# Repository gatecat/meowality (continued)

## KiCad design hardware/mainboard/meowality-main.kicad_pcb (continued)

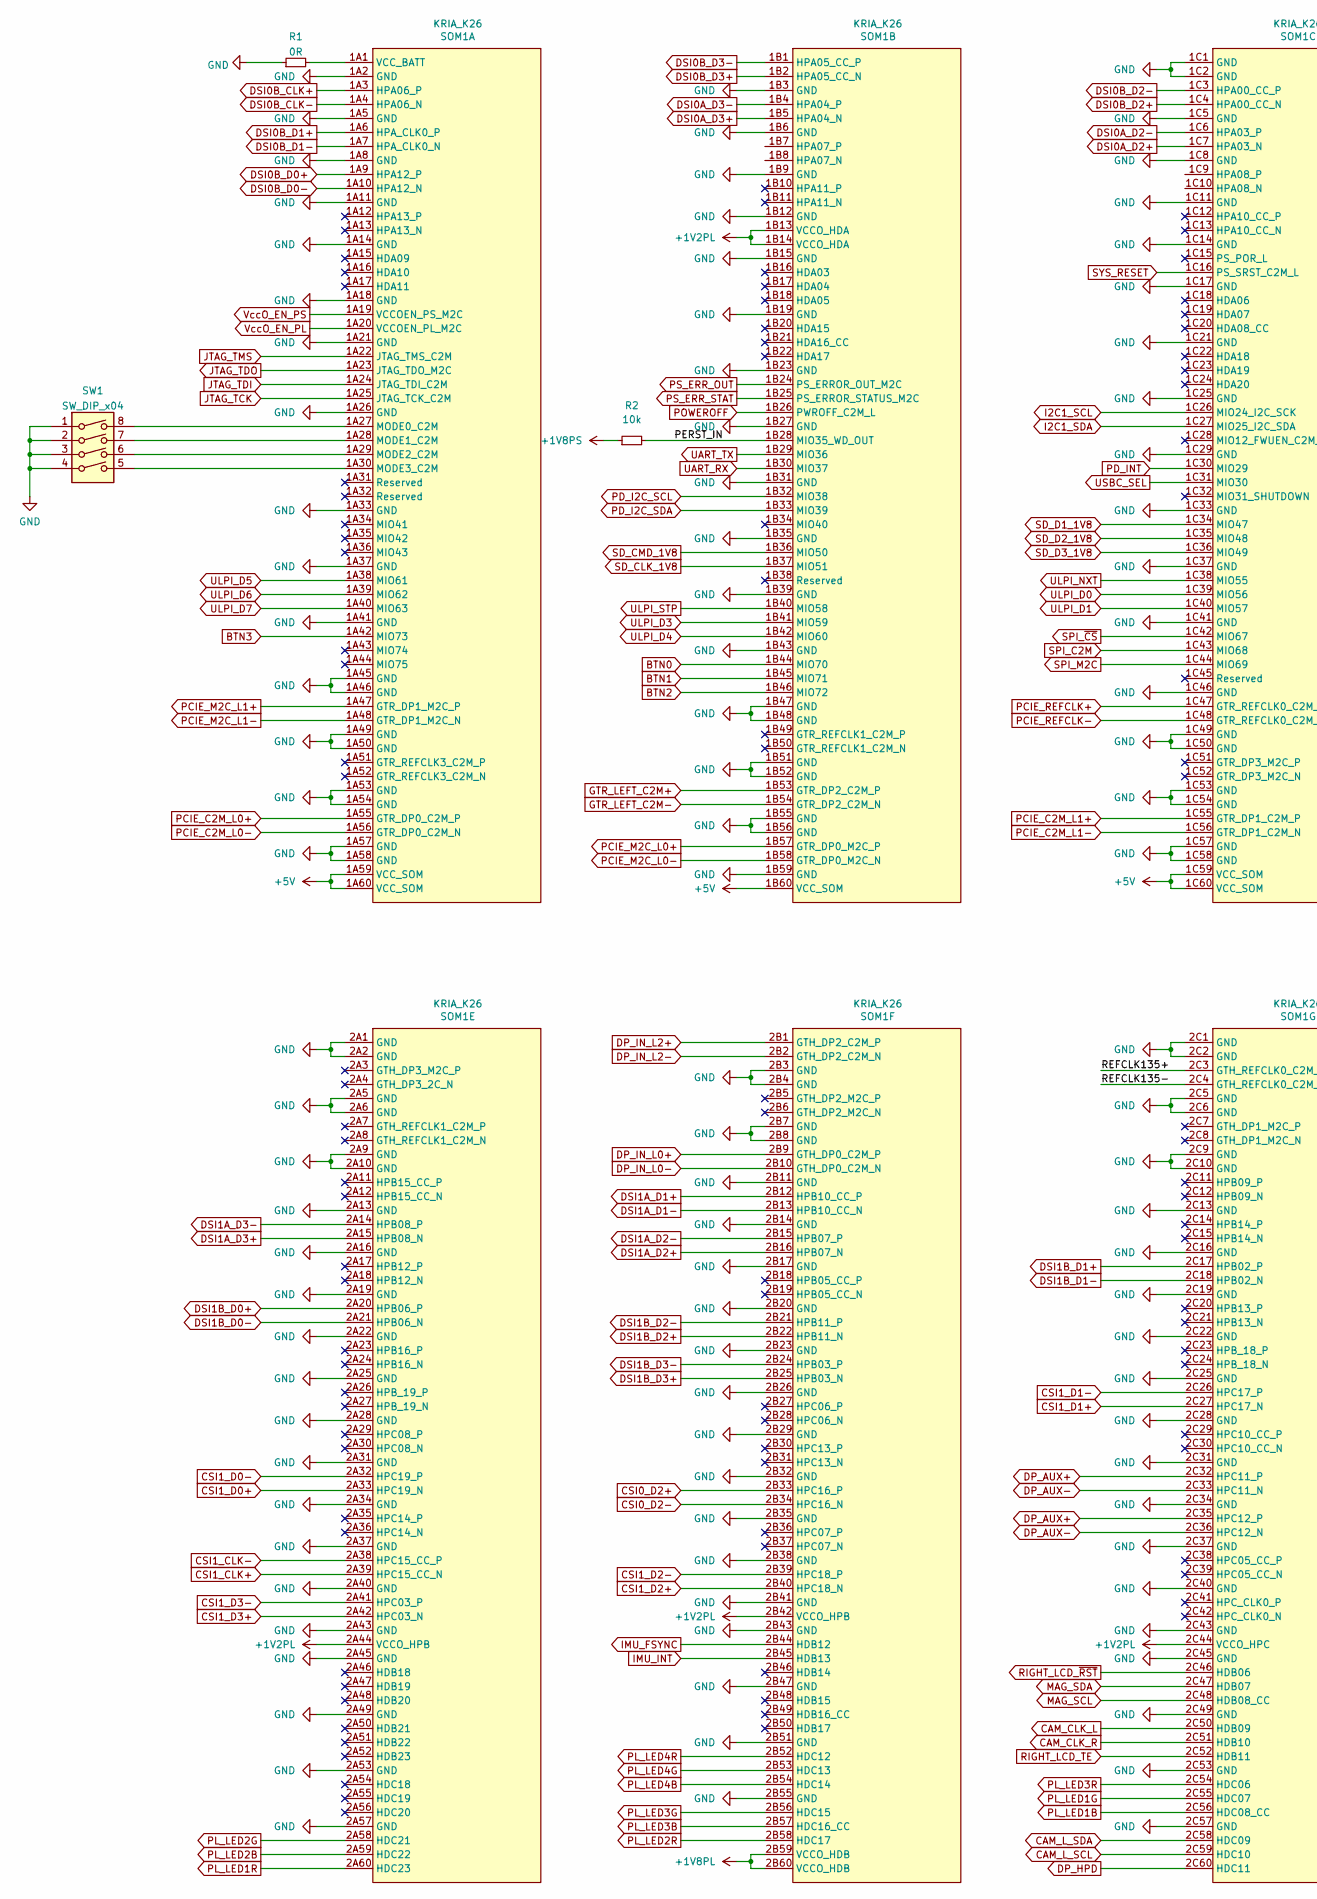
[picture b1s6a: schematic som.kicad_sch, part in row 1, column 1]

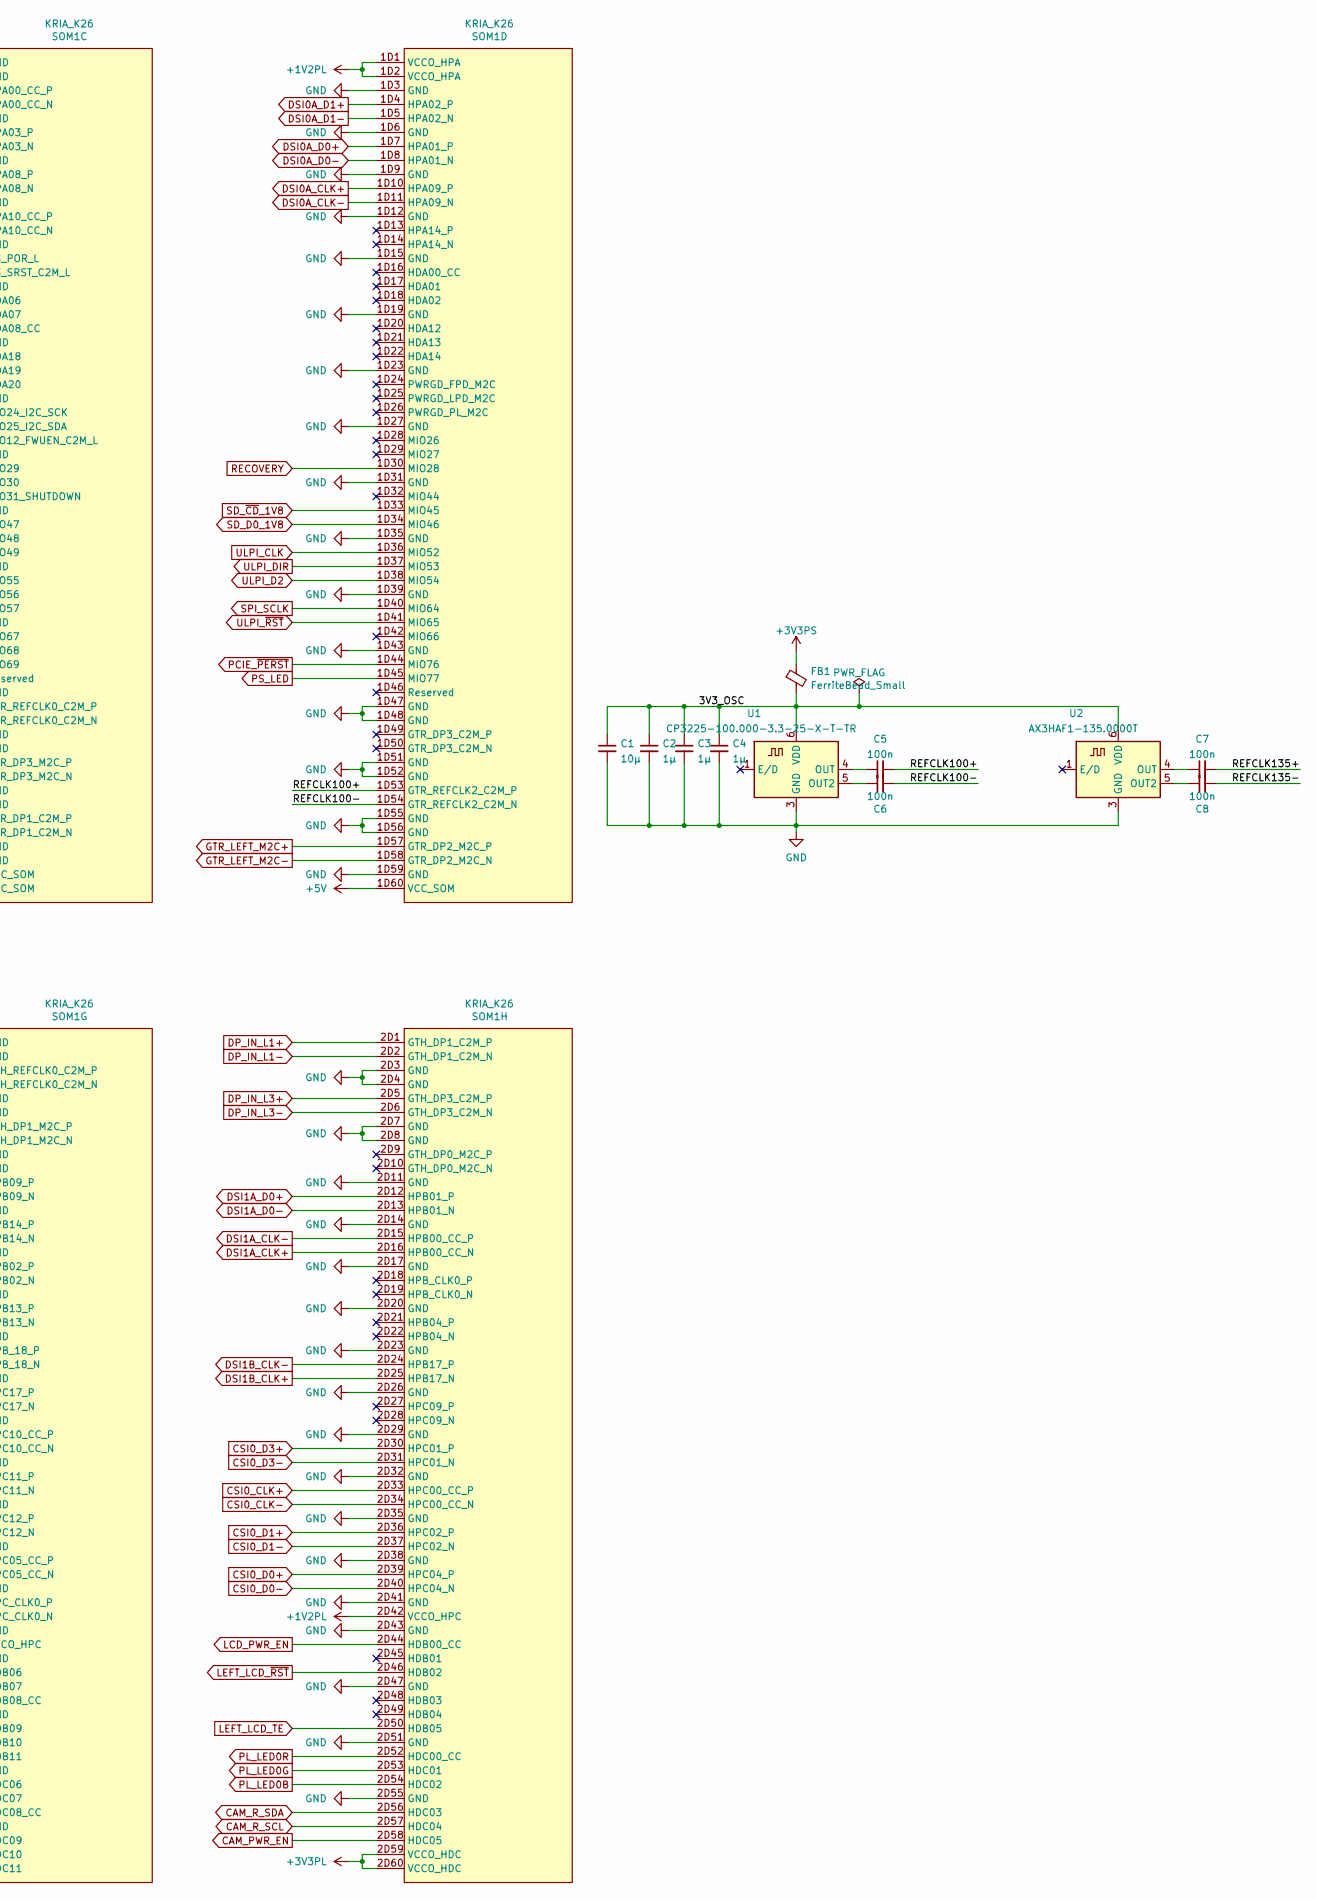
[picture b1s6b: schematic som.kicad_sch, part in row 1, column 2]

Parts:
C1: 10µ; C_1206_3216Metric
C2, C3, C4: 1µ; C_0603_1608Metric
C5, C6, C7, C8: 100n; C_0402_1005Metric
FB1: FerriteBead_Small; L_0603_1608Metric
R1: 0R; R_0402_1005Metric
R2: 10k; R_0402_1005Metric
SOM1: KRIA_K26
SW1: SW_DIP_x04; SW_DIP_SPSTx04_Slide_Copal_CHS-04B_W7.62mm_P1.27mm
U1: CP3225-100.000-3.3-25-X-T-TR; Oscillator_SMD_IDT_JS6-6_5.0x3.2mm_P1.27mm
U2: AX3HAF1-135.0000T; Oscillator_SMD_IDT_JS6-6_5.0x3.2mm_P1.27mm

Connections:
+1V2PL: SOM1.1B13 (VCCO_HDA), SOM1.1B14 (VCCO_HDA), SOM1.1D1 (VCCO_HPA), SOM1.1D2 (VCCO_HPA), SOM1.2A44 (VCCO_HPB), SOM1.2B42 (VCCO_HPB), SOM1.2C44 (VCCO_HPC), SOM1.2D42 (VCCO_HPC); also elsewhere on the board
+1V8PL: SOM1.2B59 (VCCO_HDB), SOM1.2B60 (VCCO_HDB); also elsewhere on the board
+1V8PS: R2.1; also elsewhere on the board
+3V3PL: SOM1.2D59 (VCCO_HDC), SOM1.2D60 (VCCO_HDC); also elsewhere on the board
+3V3PS: FB1.1; also elsewhere on the board
+5V: SOM1.1A59 (VCC_SOM), SOM1.1A60 (VCC_SOM), SOM1.1B60 (VCC_SOM), SOM1.1C59 (VCC_SOM), SOM1.1C60 (VCC_SOM), SOM1.1D60 (VCC_SOM); also elsewhere on the board
/SOM/3V3_OSC: C1.1, C2.1, C3.1, C4.1, FB1.2, U1.6 (VDD), U2.6 (VDD)
/SOM/PERST_IN: R2.2, SOM1.1B28 (MIO35_WD_OUT)
/SOM/REFCLK100+: C5.2, SOM1.1D53 (GTR_REFCLK2_C2M_P)
/SOM/REFCLK100-: C6.2, SOM1.1D54 (GTR_REFCLK2_C2M_N)
/SOM/REFCLK135+: C7.2, SOM1.2C3 (GTH_REFCLK0_C2M_P)
/SOM/REFCLK135-: C8.2, SOM1.2C4 (GTH_REFCLK0_C2M_N)
BTN0: SOM1.1B44 (MIO70); also elsewhere on the board
BTN1: SOM1.1B45 (MIO71); also elsewhere on the board
BTN2: SOM1.1B46 (MIO72); also elsewhere on the board
BTN3: SOM1.1A42 (MIO73); also elsewhere on the board
CAM_CLK_L: SOM1.2C50 (HDB09); also elsewhere on the board
CAM_CLK_R: SOM1.2C51 (HDB10); also elsewhere on the board
CAM_L_SCL: SOM1.2C59 (HDC10); also elsewhere on the board
CAM_L_SDA: SOM1.2C58 (HDC09); also elsewhere on the board
CAM_PWR_EN: SOM1.2D58 (HDC05); also elsewhere on the board
CAM_R_SCL: SOM1.2D57 (HDC04); also elsewhere on the board
CAM_R_SDA: SOM1.2D56 (HDC03); also elsewhere on the board
CSI0_CLK+: SOM1.2D33 (HPC00_CC_P); also elsewhere on the board
CSI0_CLK-: SOM1.2D34 (HPC00_CC_N); also elsewhere on the board
CSI0_D0+: SOM1.2D39 (HPC04_P); also elsewhere on the board
CSI0_D0-: SOM1.2D40 (HPC04_N); also elsewhere on the board
CSI0_D1+: SOM1.2D36 (HPC02_P); also elsewhere on the board
CSI0_D1-: SOM1.2D37 (HPC02_N); also elsewhere on the board
CSI0_D2+: SOM1.2B33 (HPC16_P); also elsewhere on the board
CSI0_D2-: SOM1.2B34 (HPC16_N); also elsewhere on the board
CSI0_D3+: SOM1.2D30 (HPC01_P); also elsewhere on the board
CSI0_D3-: SOM1.2D31 (HPC01_N); also elsewhere on the board
CSI1_CLK+: SOM1.2A39 (HPC15_CC_N); also elsewhere on the board
CSI1_CLK-: SOM1.2A38 (HPC15_CC_P); also elsewhere on the board
CSI1_D0+: SOM1.2A33 (HPC19_N); also elsewhere on the board
CSI1_D0-: SOM1.2A32 (HPC19_P); also elsewhere on the board
CSI1_D1+: SOM1.2C27 (HPC17_N); also elsewhere on the board
CSI1_D1-: SOM1.2C26 (HPC17_P); also elsewhere on the board
CSI1_D2+: SOM1.2B40 (HPC18_N); also elsewhere on the board
CSI1_D2-: SOM1.2B39 (HPC18_P); also elsewhere on the board
CSI1_D3+: SOM1.2A42 (HPC03_N); also elsewhere on the board
CSI1_D3-: SOM1.2A41 (HPC03_P); also elsewhere on the board
DP_AUX+: SOM1.2C32 (HPC11_P), SOM1.2C35 (HPC12_P); also elsewhere on the board
DP_AUX-: SOM1.2C33 (HPC11_N), SOM1.2C36 (HPC12_N); also elsewhere on the board
DP_HPD: SOM1.2C60 (HDC11); also elsewhere on the board
DP_IN_L0+: SOM1.2B9 (GTH_DP0_C2M_P); also elsewhere on the board
DP_IN_L0-: SOM1.2B10 (GTH_DP0_C2M_N); also elsewhere on the board
DP_IN_L1+: SOM1.2D1 (GTH_DP1_C2M_P); also elsewhere on the board
DP_IN_L1-: SOM1.2D2 (GTH_DP1_C2M_N); also elsewhere on the board
DP_IN_L2+: SOM1.2B1 (GTH_DP2_C2M_P); also elsewhere on the board
DP_IN_L2-: SOM1.2B2 (GTH_DP2_C2M_N); also elsewhere on the board
DP_IN_L3+: SOM1.2D5 (GTH_DP3_C2M_P); also elsewhere on the board
DP_IN_L3-: SOM1.2D6 (GTH_DP3_C2M_N); also elsewhere on the board
DSI0A_CLK+: SOM1.1D10 (HPA09_P); also elsewhere on the board
DSI0A_CLK-: SOM1.1D11 (HPA09_N); also elsewhere on the board
DSI0A_D0+: SOM1.1D7 (HPA01_P); also elsewhere on the board
DSI0A_D0-: SOM1.1D8 (HPA01_N); also elsewhere on the board
DSI0A_D1+: SOM1.1D4 (HPA02_P); also elsewhere on the board
DSI0A_D1-: SOM1.1D5 (HPA02_N); also elsewhere on the board
DSI0A_D2+: SOM1.1C7 (HPA03_N); also elsewhere on the board
DSI0A_D2-: SOM1.1C6 (HPA03_P); also elsewhere on the board
DSI0A_D3+: SOM1.1B5 (HPA04_N); also elsewhere on the board
DSI0A_D3-: SOM1.1B4 (HPA04_P); also elsewhere on the board
DSI0B_CLK+: SOM1.1A3 (HPA06_P); also elsewhere on the board
DSI0B_CLK-: SOM1.1A4 (HPA06_N); also elsewhere on the board
DSI0B_D0+: SOM1.1A9 (HPA12_P); also elsewhere on the board
DSI0B_D0-: SOM1.1A10 (HPA12_N); also elsewhere on the board
DSI0B_D1+: SOM1.1A6 (HPA_CLK0_P); also elsewhere on the board
DSI0B_D1-: SOM1.1A7 (HPA_CLK0_N); also elsewhere on the board
DSI0B_D2+: SOM1.1C4 (HPA00_CC_N); also elsewhere on the board
DSI0B_D2-: SOM1.1C3 (HPA00_CC_P); also elsewhere on the board
DSI0B_D3+: SOM1.1B2 (HPA05_CC_N); also elsewhere on the board
DSI0B_D3-: SOM1.1B1 (HPA05_CC_P); also elsewhere on the board
DSI1A_CLK+: SOM1.2D16 (HPB00_CC_N); also elsewhere on the board
DSI1A_CLK-: SOM1.2D15 (HPB00_CC_P); also elsewhere on the board
DSI1A_D0+: SOM1.2D12 (HPB01_P); also elsewhere on the board
DSI1A_D0-: SOM1.2D13 (HPB01_N); also elsewhere on the board
DSI1A_D1+: SOM1.2B12 (HPB10_CC_P); also elsewhere on the board
DSI1A_D1-: SOM1.2B13 (HPB10_CC_N); also elsewhere on the board
DSI1A_D2+: SOM1.2B16 (HPB07_N); also elsewhere on the board
DSI1A_D2-: SOM1.2B15 (HPB07_P); also elsewhere on the board
DSI1A_D3+: SOM1.2A15 (HPB08_N); also elsewhere on the board
DSI1A_D3-: SOM1.2A14 (HPB08_P); also elsewhere on the board
DSI1B_CLK+: SOM1.2D25 (HPB17_N); also elsewhere on the board
DSI1B_CLK-: SOM1.2D24 (HPB17_P); also elsewhere on the board
DSI1B_D0+: SOM1.2A20 (HPB06_P); also elsewhere on the board
DSI1B_D0-: SOM1.2A21 (HPB06_N); also elsewhere on the board
DSI1B_D1+: SOM1.2C17 (HPB02_P); also elsewhere on the board
DSI1B_D1-: SOM1.2C18 (HPB02_N); also elsewhere on the board
DSI1B_D2+: SOM1.2B22 (HPB11_N); also elsewhere on the board
DSI1B_D2-: SOM1.2B21 (HPB11_P); also elsewhere on the board
DSI1B_D3+: SOM1.2B25 (HPB03_N); also elsewhere on the board
DSI1B_D3-: SOM1.2B24 (HPB03_P); also elsewhere on the board
GND: C1.2, C2.2, C3.2, C4.2, R1.1, SOM1.1A2 (GND), SOM1.1A5 (GND), SOM1.1A8 (GND), SOM1.1A11 (GND), SOM1.1A14 (GND), SOM1.1A18 (GND), SOM1.1A21 (GND), SOM1.1A26 (GND), SOM1.1A33 (GND), SOM1.1A37 (GND), SOM1.1A41 (GND), SOM1.1A45 (GND), SOM1.1A46 (GND), SOM1.1A49 (GND), SOM1.1A50 (GND), SOM1.1A53 (GND), SOM1.1A54 (GND), SOM1.1A57 (GND), SOM1.1A58 (GND), SOM1.1B3 (GND), SOM1.1B6 (GND), SOM1.1B9 (GND), SOM1.1B12 (GND), SOM1.1B15 (GND), SOM1.1B19 (GND), SOM1.1B23 (GND), SOM1.1B27 (GND), SOM1.1B31 (GND), SOM1.1B35 (GND), SOM1.1B39 (GND), SOM1.1B43 (GND), SOM1.1B47 (GND), SOM1.1B48 (GND), SOM1.1B51 (GND), SOM1.1B52 (GND), SOM1.1B55 (GND), SOM1.1B56 (GND), SOM1.1B59 (GND), SOM1.1C1 (GND), SOM1.1C2 (GND), SOM1.1C5 (GND), SOM1.1C8 (GND), SOM1.1C11 (GND), SOM1.1C14 (GND), SOM1.1C17 (GND), SOM1.1C21 (GND), SOM1.1C25 (GND), SOM1.1C29 (GND), SOM1.1C33 (GND), SOM1.1C37 (GND), SOM1.1C41 (GND), SOM1.1C46 (GND), SOM1.1C49 (GND), SOM1.1C50 (GND), SOM1.1C53 (GND), SOM1.1C54 (GND), SOM1.1C57 (GND), SOM1.1C58 (GND), SOM1.1D3 (GND), SOM1.1D6 (GND), SOM1.1D9 (GND), SOM1.1D12 (GND), SOM1.1D15 (GND), SOM1.1D19 (GND), SOM1.1D23 (GND), SOM1.1D27 (GND), SOM1.1D31 (GND), SOM1.1D35 (GND), SOM1.1D39 (GND), SOM1.1D43 (GND), SOM1.1D47 (GND), SOM1.1D48 (GND), SOM1.1D51 (GND), SOM1.1D52 (GND), SOM1.1D55 (GND), SOM1.1D56 (GND), SOM1.1D59 (GND), SOM1.2A1 (GND), SOM1.2A2 (GND), SOM1.2A5 (GND), SOM1.2A6 (GND), SOM1.2A9 (GND), SOM1.2A10 (GND), SOM1.2A13 (GND), SOM1.2A16 (GND), SOM1.2A19 (GND), SOM1.2A22 (GND), SOM1.2A25 (GND), SOM1.2A28 (GND), SOM1.2A31 (GND), SOM1.2A34 (GND), SOM1.2A37 (GND), SOM1.2A40 (GND), SOM1.2A43 (GND), SOM1.2A45 (GND), SOM1.2A49 (GND), SOM1.2A53 (GND), SOM1.2A57 (GND), SOM1.2B3 (GND), SOM1.2B4 (GND), SOM1.2B7 (GND), SOM1.2B8 (GND), SOM1.2B11 (GND), SOM1.2B14 (GND), SOM1.2B17 (GND), SOM1.2B20 (GND), SOM1.2B23 (GND), SOM1.2B26 (GND), SOM1.2B29 (GND), SOM1.2B32 (GND), SOM1.2B35 (GND), SOM1.2B38 (GND), SOM1.2B41 (GND), SOM1.2B43 (GND), SOM1.2B47 (GND), SOM1.2B51 (GND), SOM1.2B55 (GND), SOM1.2C1 (GND), SOM1.2C2 (GND), SOM1.2C5 (GND), SOM1.2C6 (GND), SOM1.2C9 (GND), SOM1.2C10 (GND), SOM1.2C13 (GND), SOM1.2C16 (GND), SOM1.2C19 (GND), SOM1.2C22 (GND), SOM1.2C25 (GND), SOM1.2C28 (GND), SOM1.2C31 (GND), SOM1.2C34 (GND), SOM1.2C37 (GND), SOM1.2C40 (GND), SOM1.2C43 (GND), SOM1.2C45 (GND), SOM1.2C49 (GND), SOM1.2C53 (GND), SOM1.2C57 (GND), SOM1.2D3 (GND), SOM1.2D4 (GND), SOM1.2D7 (GND), SOM1.2D8 (GND), SOM1.2D11 (GND), SOM1.2D14 (GND), SOM1.2D17 (GND), SOM1.2D20 (GND), SOM1.2D23 (GND), SOM1.2D26 (GND), SOM1.2D29 (GND), SOM1.2D32 (GND), SOM1.2D35 (GND), SOM1.2D38 (GND), SOM1.2D41 (GND), SOM1.2D43 (GND), SOM1.2D47 (GND), SOM1.2D51 (GND), SOM1.2D55 (GND), SW1.1, SW1.2, SW1.3, SW1.4, U1.3 (GND), U2.3 (GND); also elsewhere on the board
GTR_LEFT_C2M+: SOM1.1B53 (GTR_DP2_C2M_P); also elsewhere on the board
GTR_LEFT_C2M-: SOM1.1B54 (GTR_DP2_C2M_N); also elsewhere on the board
GTR_LEFT_M2C+: SOM1.1D57 (GTR_DP2_M2C_P); also elsewhere on the board
GTR_LEFT_M2C-: SOM1.1D58 (GTR_DP2_M2C_N); also elsewhere on the board
I2C1_SCL: SOM1.1C26 (MIO24_I2C_SCK); also elsewhere on the board
I2C1_SDA: SOM1.1C27 (MIO25_I2C_SDA); also elsewhere on the board
IMU_FSYNC: SOM1.2B44 (HDB12); also elsewhere on the board
IMU_INT: SOM1.2B45 (HDB13); also elsewhere on the board
JTAG_TCK: SOM1.1A25 (JTAG_TCK_C2M); also elsewhere on the board
JTAG_TDI: SOM1.1A24 (JTAG_TDI_C2M); also elsewhere on the board
JTAG_TDO: SOM1.1A23 (JTAG_TDO_M2C); also elsewhere on the board
JTAG_TMS: SOM1.1A22 (JTAG_TMS_C2M); also elsewhere on the board
LCD_PWR_EN: SOM1.2D44 (HDB00_CC); also elsewhere on the board
LEFT_LCD_TE: SOM1.2D50 (HDB05); also elsewhere on the board
LEFT_LCD_~RST: SOM1.2D46 (HDB02); also elsewhere on the board
MAG_SCL: SOM1.2C48 (HDB08_CC); also elsewhere on the board
MAG_SDA: SOM1.2C47 (HDB07); also elsewhere on the board
unnamed: C5.1, U1.4 (OUT)
unnamed: C6.1, U1.5 (OUT2)
unnamed: C7.1, U2.4 (OUT)
unnamed: C8.1, U2.5 (OUT2)
unnamed: R1.2, SOM1.1A1 (VCC_BATT)
unnamed: SOM1.1A27 (MODE0_C2M), SW1.8
unnamed: SOM1.1A28 (MODE1_C2M), SW1.7
unnamed: SOM1.1A29 (MODE2_C2M), SW1.6
unnamed: SOM1.1A30 (MODE3_C2M), SW1.5
PCIE_C2M_L0+: SOM1.1A55 (GTR_DP0_C2M_P); also elsewhere on the board
PCIE_C2M_L0-: SOM1.1A56 (GTR_DP0_C2M_N); also elsewhere on the board
PCIE_C2M_L1+: SOM1.1C55 (GTR_DP1_C2M_P); also elsewhere on the board
PCIE_C2M_L1-: SOM1.1C56 (GTR_DP1_C2M_N); also elsewhere on the board
PCIE_M2C_L0+: SOM1.1B57 (GTR_DP0_M2C_P); also elsewhere on the board
PCIE_M2C_L0-: SOM1.1B58 (GTR_DP0_M2C_N); also elsewhere on the board
PCIE_M2C_L1+: SOM1.1A47 (GTR_DP1_M2C_P); also elsewhere on the board
PCIE_M2C_L1-: SOM1.1A48 (GTR_DP1_M2C_N); also elsewhere on the board
PCIE_REFCLK+: SOM1.1C47 (GTR_REFCLK0_C2M_P); also elsewhere on the board
PCIE_REFCLK-: SOM1.1C48 (GTR_REFCLK0_C2M_N); also elsewhere on the board
PCIE_~PERST: SOM1.1D44 (MIO76); also elsewhere on the board
PD_I2C_SCL: SOM1.1B32 (MIO38); also elsewhere on the board
PD_I2C_SDA: SOM1.1B33 (MIO39); also elsewhere on the board
PD_INT: SOM1.1C30 (MIO29); also elsewhere on the board
PL_LED0B: SOM1.2D54 (HDC02); also elsewhere on the board
PL_LED0G: SOM1.2D53 (HDC01); also elsewhere on the board
PL_LED0R: SOM1.2D52 (HDC00_CC); also elsewhere on the board
PL_LED1B: SOM1.2C56 (HDC08_CC); also elsewhere on the board
PL_LED1G: SOM1.2C55 (HDC07); also elsewhere on the board
PL_LED1R: SOM1.2A60 (HDC23); also elsewhere on the board
PL_LED2B: SOM1.2A59 (HDC22); also elsewhere on the board
PL_LED2G: SOM1.2A58 (HDC21); also elsewhere on the board
PL_LED2R: SOM1.2B58 (HDC17); also elsewhere on the board
PL_LED3B: SOM1.2B57 (HDC16_CC); also elsewhere on the board
PL_LED3G: SOM1.2B56 (HDC15); also elsewhere on the board
PL_LED3R: SOM1.2C54 (HDC06); also elsewhere on the board
PL_LED4B: SOM1.2B54 (HDC14); also elsewhere on the board
PL_LED4G: SOM1.2B53 (HDC13); also elsewhere on the board
PL_LED4R: SOM1.2B52 (HDC12); also elsewhere on the board
POWEROFF: SOM1.1B26 (PWROFF_C2M_L); also elsewhere on the board
PS_ERR_OUT: SOM1.1B24 (PS_ERROR_OUT_M2C); also elsewhere on the board
PS_ERR_STAT: SOM1.1B25 (PS_ERROR_STATUS_M2C); also elsewhere on the board
PS_LED: SOM1.1D45 (MIO77); also elsewhere on the board
RECOVERY: SOM1.1D30 (MIO28); also elsewhere on the board
RIGHT_LCD_TE: SOM1.2C52 (HDB11); also elsewhere on the board
RIGHT_LCD_~RST: SOM1.2C46 (HDB06); also elsewhere on the board
SD_CLK_1V8: SOM1.1B37 (MIO51); also elsewhere on the board
SD_CMD_1V8: SOM1.1B36 (MIO50); also elsewhere on the board
SD_D0_1V8: SOM1.1D34 (MIO46); also elsewhere on the board
SD_D1_1V8: SOM1.1C34 (MIO47); also elsewhere on the board
SD_D2_1V8: SOM1.1C35 (MIO48); also elsewhere on the board
SD_D3_1V8: SOM1.1C36 (MIO49); also elsewhere on the board
SD_~CD_1V8: SOM1.1D33 (MIO45); also elsewhere on the board
SPI_C2M: SOM1.1C43 (MIO68); also elsewhere on the board
SPI_M2C: SOM1.1C44 (MIO69); also elsewhere on the board
SPI_SCLK: SOM1.1D40 (MIO64); also elsewhere on the board
SPI_~CS: SOM1.1C42 (MIO67); also elsewhere on the board
SYS_RESET: SOM1.1C16 (PS_SRST_C2M_L); also elsewhere on the board
UART_RX: SOM1.1B30 (MIO37); also elsewhere on the board
UART_TX: SOM1.1B29 (MIO36); also elsewhere on the board
ULPI_CLK: SOM1.1D36 (MIO52); also elsewhere on the board
ULPI_D0: SOM1.1C39 (MIO56); also elsewhere on the board
ULPI_D1: SOM1.1C40 (MIO57); also elsewhere on the board
ULPI_D2: SOM1.1D38 (MIO54); also elsewhere on the board
ULPI_D3: SOM1.1B41 (MIO59); also elsewhere on the board
ULPI_D4: SOM1.1B42 (MIO60); also elsewhere on the board
ULPI_D5: SOM1.1A38 (MIO61); also elsewhere on the board
ULPI_D6: SOM1.1A39 (MIO62); also elsewhere on the board
ULPI_D7: SOM1.1A40 (MIO63); also elsewhere on the board
ULPI_DIR: SOM1.1D37 (MIO53); also elsewhere on the board
ULPI_NXT: SOM1.1C38 (MIO55); also elsewhere on the board
ULPI_STP: SOM1.1B40 (MIO58); also elsewhere on the board
ULPI_~RST: SOM1.1D41 (MIO65); also elsewhere on the board
USBC_SEL: SOM1.1C31 (MIO30); also elsewhere on the board
VccO_EN_PL: SOM1.1A20 (VCCOEN_PL_M2C); also elsewhere on the board
VccO_EN_PS: SOM1.1A19 (VCCOEN_PS_M2C); also elsewhere on the board

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
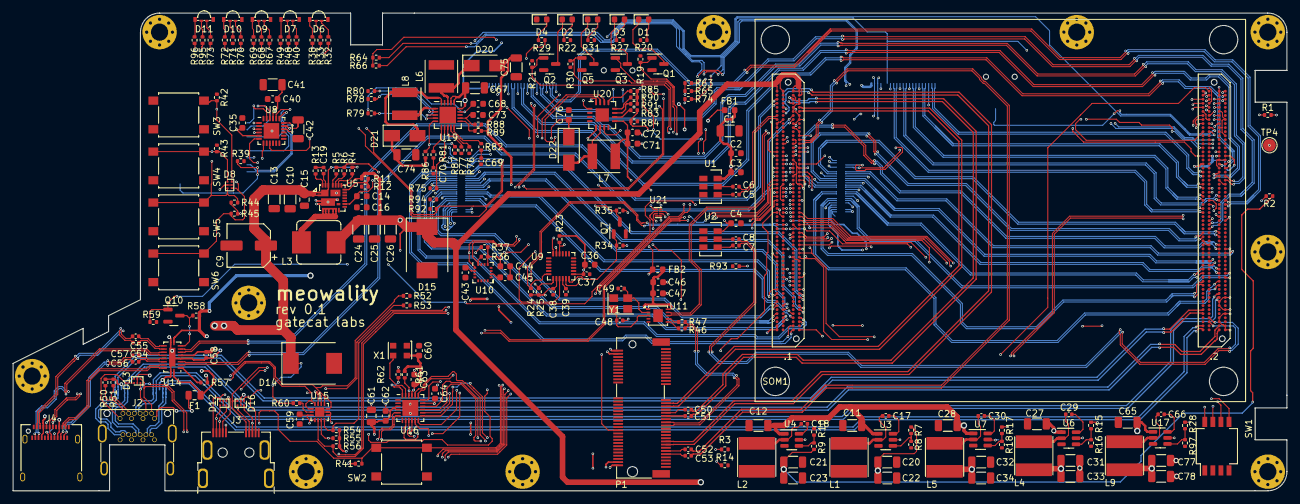
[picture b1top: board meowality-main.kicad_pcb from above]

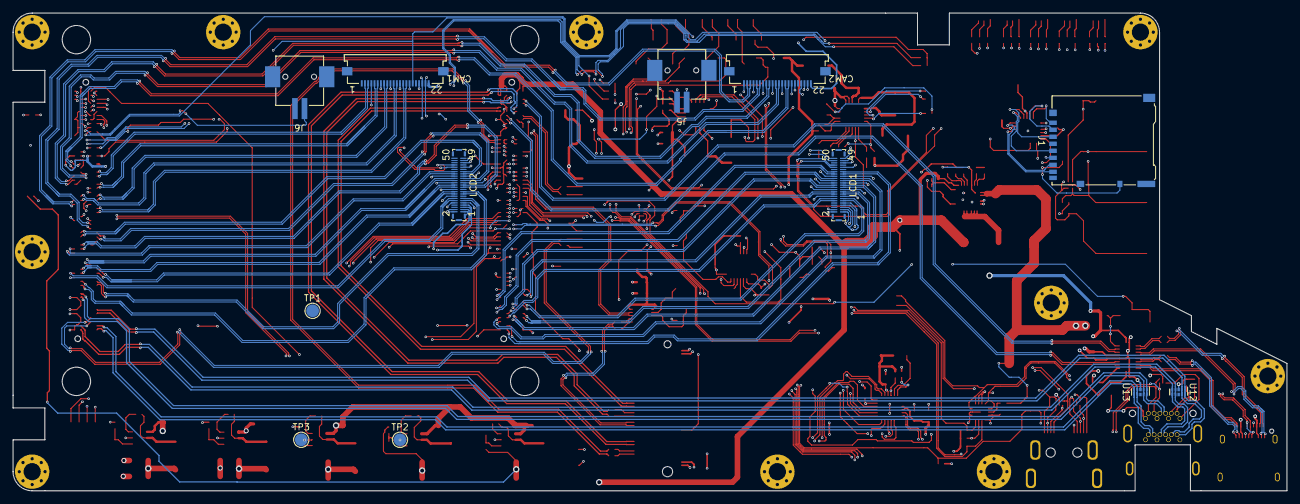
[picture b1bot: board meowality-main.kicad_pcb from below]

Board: 6 copper layers, 200.0 x 75.0 mm, 265 parts (12 on the bottom side), 313 nets.
